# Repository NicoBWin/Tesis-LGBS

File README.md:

# Tesis-LGBS

Es el repositorio para la materia _Diseño de equipos electronico - 22.31_. Se basa en un Inverter de Corriente o también conocido como Convertidor Modular Multinivel de Corriente. El repo se divide en carpetas según los hitos que se fueron presentando, asi como tambíen se divide en diferentes carpeta segun reuniones, avance, o prototipado.

**Comienzo:** 06/03/2024

**Finalización:** ??/??/????

## Equipo

-   Linares, Gonzalo
-   Gullino, Agustín
-   Bustelo, Nicolás
-   Sergi, Damián

## Tutores

-   Aguirre, Pablo Miguel
-   Cossutta, Pablo Martín

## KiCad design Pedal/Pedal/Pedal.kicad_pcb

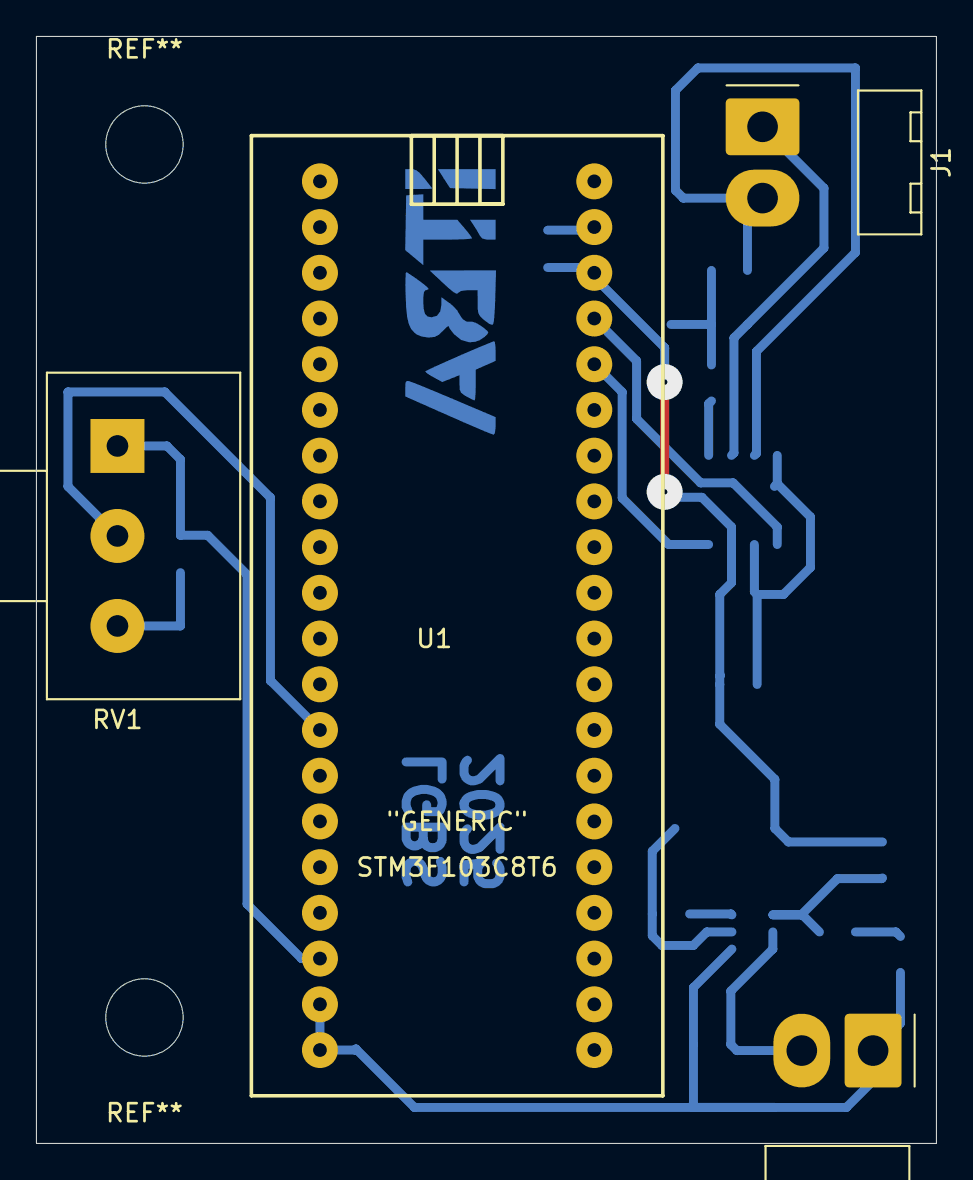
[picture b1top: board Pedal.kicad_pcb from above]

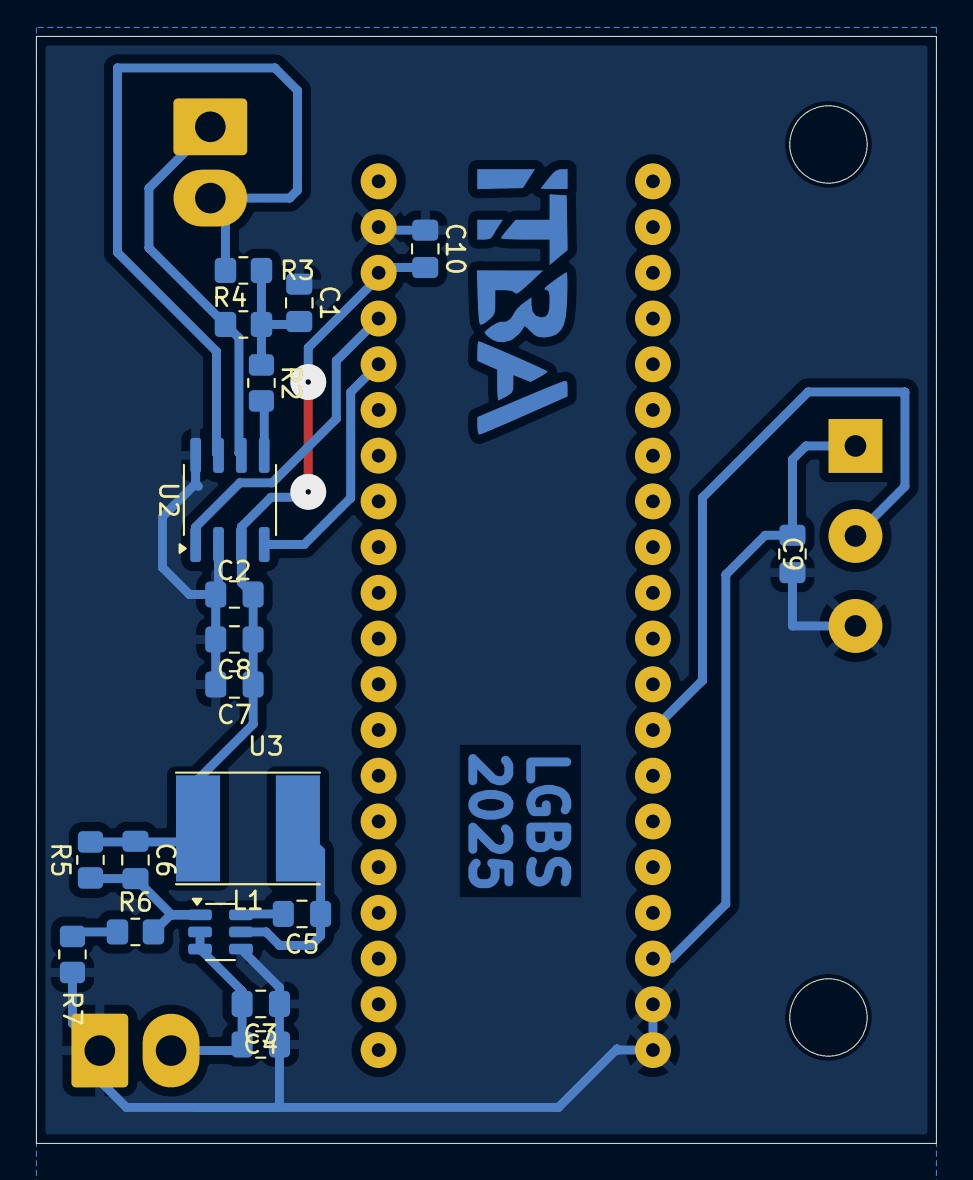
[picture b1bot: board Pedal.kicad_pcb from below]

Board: 2 copper layers, 50.0 x 61.5 mm, 23 parts (19 on the bottom side), 15 nets.

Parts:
C1: 4.7nF; C_0805_2012Metric_Pad1.18x1.45mm_HandSolder
C2, C3, C5, C9: 100nF; C_0805_2012Metric_Pad1.18x1.45mm_HandSolder
C4, C7, C8: 10uF; C_0805_2012Metric_Pad1.18x1.45mm_HandSolder
C6: 100pF; C_0805_2012Metric_Pad1.18x1.45mm_HandSolder
C10: 1uF; C_0805_2012Metric_Pad1.18x1.45mm_HandSolder
J1, J2: Conn_01x02; Molex_KK-396_A-41792-0002_1x02_P3.96mm_Horizontal
L1: 10uH; L_Taiyo-Yuden_NR-60xx_HandSoldering
R2: 300; R_0805_2012Metric_Pad1.20x1.40mm_HandSolder
R3, R4: 61; R_0805_2012Metric_Pad1.20x1.40mm_HandSolder
R5: 10k; R_0805_2012Metric_Pad1.20x1.40mm_HandSolder
R6: 1.8k; R_0805_2012Metric_Pad1.20x1.40mm_HandSolder
R7: 100; R_0805_2012Metric_Pad1.20x1.40mm_HandSolder
RV1: 100k; Potentiometer_Alps_RK163_Single_Horizontal
U1: YAAJ_BluePill_Part_Like; BLUEPILL
U2: MCP2561-E-SN; SOIC-8_3.9x4.9mm_P1.27mm
U3: AP63200WU; TSOT-23-6

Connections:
+3.3V: C9.1, RV1.1, U1.38 (3V3)
+5V: C2.1, C6.1, C7.1, C8.1, C10.2, L1.2, R5.2, U1.18 (5V), U2.3 (VDD)
+24V: C3.2, C4.2, J2.2, U3.2 (EN), U3.3 (IN)
CAN_RXD: U1.16 (PB8), U2.4 (RXD)
CAN_TXD: U1.17 (PB9), U2.1 (TXD)
GND: C1.1, C2.2, C3.1, C4.1, C7.2, C8.2, C9.2, C10.1, J2.1, R7.1, RV1.3, U1.19 (GND), U1.39 (GND), U1.40 (GND), U2.2 (VSS), U2.8 (STBY), U3.4 (GND)
unnamed: C1.2, R2.1, R3.1, R4.2
unnamed: J1.1, R4.1, U2.6 (CANL)
unnamed: J1.2, R3.2, U2.7 (CANH)
unnamed: R6.1, R7.2
unnamed: R2.2, U2.5 (SPLIT)
unnamed: C5.2, U3.6 (BST)
unnamed: C6.2, R5.1, R6.2, U3.1 (FB)
unnamed: C5.1, L1.1, U3.5 (SW)
POT_VALUE: RV1.2, U1.33 (PB0)

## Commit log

2024-03-29 add papers
2024-05-14 ReunionMiguel
2024-05-14 Arreglo al apunte de reunion de Miguel 13-05
2024-05-16 datasheet motor, preguntas a miguel, papers
2024-05-23 clase consultas 22-05
2024-05-23 Added Excel Trazabilidad
2024-05-24 add presentacion hito 1 and modify readme
2024-06-01 Acomodar
2024-06-08 Add Hito1
2024-08-13 actualización de comentarios.
2024-08-23 Reunión 23-08-24
2024-09-27 added some dummy files
2024-09-29 evironment created
2024-09-29 a ver si anda
2024-09-29 ahi lo arregle
2024-09-29 move .env
2024-09-29 moved some files
2024-09-29 probando
2024-09-29 ahora anda
2024-09-29 some updates
2024-09-29 UART ready to test
2024-09-29 estoy programando el top-v para hacer un lookback
2024-10-05 bueno, todavia no me anda
2024-10-05 reverted .pfc
2024-10-05 added tb
2024-10-05 creo que la transmision anda
2024-10-05 falta que ande la RX
2024-10-06 a ver si ahora anda
2024-10-06 probando...
2024-10-07 todavia no anda, esta raro
2024-10-07 ahora anda mejor
2024-10-10 generator created
2024-10-12 some changes
2024-10-12 now tx works better
2024-10-14 testing rx
2024-10-15 trying to program generators
2024-10-15 added generator
2024-10-16 no se que le pasa a la frecuencia
2024-10-16 listo
2024-10-18 pingocha
2024-10-18 agregamos papers
2024-10-20 updated tx
2024-10-20 phase gen erased
2024-10-20 uart tx refactored
2024-10-20 a ver
2024-10-20 reverted tx
2024-10-20 esta version puede que este mejor
2024-10-20 ready rx to test
2024-10-21 added docs
2024-10-21 trying to redo generator
2024-10-21 ready to test uart
2024-10-21 utils clk divider needs to be fixed
2024-10-21 added shift register
2024-10-27 se podria probar ya el ADC
2024-10-27 listo XD
2024-10-27 minor changes
2024-10-28 modifique tx
2024-10-31 test
2024-10-31 added tbs
2024-10-31 moved some code
2024-10-31 modifed makefiles
2024-10-31 fixed ADC
2024-10-31 hice lo que se pudio
2024-11-02 probemos esto
2024-11-02 agregamos archivos de matlab
2024-11-07 cambios que hizo gonza el sabado en el cidei
2024-11-08 read main to test
2024-11-08 folders for hitos
2024-11-08 to-do
2024-11-09 ToDo_Modificacion
2024-11-09 listo el adc
2024-11-09 Reorganizacion
2024-11-09 Arreglito
2024-11-09 Reorganizacion 2.0
2024-11-16 fixed
2024-11-16 erased const source
2024-11-16 ready uart
2024-11-23 some changes in makefile
2024-11-25 mejorando UART
2024-11-26 no changes
2024-11-26 mejore la velocidad pero no anda mejor el transmisor
2024-11-26 added manchester
2024-11-27 erased
2024-11-27 no andaaa nadaa
2024-11-27 el uart de springler
2024-11-27 reverted UART
2024-11-27 nada
2024-12-01 matlab changes
2024-12-01 changes in tx and rx
2024-12-01 added hamming code
2024-12-02 modificando RX
2024-12-04 anda muuucho mejor
2024-12-04 anda raro algo del receptor
2024-12-20 Matlab Modulation is ready to test
2024-12-24 seguimo' sumando codigo del SPI
2024-12-29 testing
2025-01-03 tested
2025-01-03 haciendo el top main FPGA
2025-01-03 ready to verify
2025-01-03 verified
2025-01-04 Blackpill folder erased
2025-01-06 writing pipe
2025-01-08 updated matlab hdl model
2025-01-08 matlab update
2025-01-09 writing modules
2025-01-11 programming modules
2025-01-11 added tasks to modules
2025-01-11 spi_tb updated
2025-01-16 changes in schematic
2025-01-17 modifying main FPGA
2025-01-17 added more lines
2025-01-17 no creo que ande esto
2025-01-18 La modulacion tiene un revamp
2025-01-18 modifications in uart_tx
2025-01-18 te subo el RX
2025-01-18 codigo
2025-01-18 mira
2025-01-18 anda RX
2025-01-19 subo
2025-01-19 cuack
2025-01-19 parece andar
2025-01-21 Actualiza el Makefile y módulos UART para mejorar la transmisión y recepción de datos
2025-01-21 Corrige la señal de reloj en el módulo uart_tx y actualiza la asignación de pines en top_UART_TX
2025-01-21 Modifica el estado inicial en el módulo uart_tx y actualiza la asignación de pines en top_UART_TX
2025-01-21 tengo que revisar la task ....
2025-01-22 Actualiza la tasa de baudios a 6M en el módulo top_UART_TX y simplifica la lógica de finalización de transmisión
2025-01-22 Actualiza el Makefile y módulos UART para cambiar la tasa de baudios a 1M y renombrar el módulo de prueba
2025-01-22 Crea el módulo top_UART_loopback y actualiza el Makefile para incluirlo, además de modificar la asignación de pines en el módulo de prueba.
2025-01-22 Modifica el módulo uart_rx para ampliar el tamaño del estado y añade el estado RX_DONE. Actualiza la lógica en top_UART_loopback para manejar la transmisión y recepción de datos correctamente.
2025-01-25 ultima
2025-01-25 Actualiza el Makefile y los módulos de prueba UART para corregir la asignación de pines y ajustar la lógica de temporización.
2025-01-25 Actualiza el Makefile y modifica el módulo top_prueba_UART_UB para corregir la lógica de transmisión y recepción de datos.
2025-01-25 Actualiza el Makefile y modifica los módulos de prueba UART para corregir la asignación de nombres y mejorar la lógica de transmisión.
2025-01-25 Actualiza la configuración del oscilador y la tasa de baudios en los módulos de prueba UART.
2025-01-25 Actualiza el Makefile y los módulos de prueba UART para corregir la asignación de nombres y ajustar la configuración del oscilador y la tasa de baudios.
2025-01-25 Modifica la lógica de recepción y transmisión en los módulos UART para mejorar el manejo de estados y la sincronización de señales.
2025-01-25 Reorganiza la asignación de señales en el módulo de prueba UART para mejorar la claridad y el manejo de datos recibidos.
2025-01-27 1Mb/s varios cambios
2025-02-01 UART_Avances6Mb/s
2025-02-01 Mejor documentado UART
    UART funciona a 6Mb/s de forma constante pero con STOP = 2
2025-02-01 review SPI
2025-02-01 Renombra el estado DESELECT a DONE en el módulo SPI para mejorar la claridad del flujo de estado.
2025-02-01 Add top module for SPI and update clock rates; remove unused UART_RX module
2025-02-02 Add PRAM module and update top module to replace RAM; refactor SPI connections
2025-02-03 Add schematics
2025-02-07 no anda spi
2025-02-08 test ready
2025-02-08 updated SPI
2025-02-09 cambios en sclk
2025-02-09 reverted
2025-02-19 agregue codigo en la fpga main
2025-02-22 micro
2025-02-22 Simulations with real current source and ajusted correctly the pins used
2025-02-22 SPI_Funciona el codigo nuevo masomenos
2025-02-22 CAN SPI
2025-02-23 added a pram testbench
2025-02-23 ready PRAM
2025-03-01 Test Main current source
2025-03-01 Add MAX_CURR constant and input validation in set_I function
2025-03-01 done current
2025-03-03 Some sims update
2025-03-05 ytfytd
2025-03-07 casi casi
2025-03-07 bueno, listo por hoy
2025-03-08 add binary files and history for Tesis_LGBS project
2025-03-08 escribiendo el main PFAGA
2025-03-08 added maximum calc
2025-03-08 Add mediciones
    Just Buck & Flyback
2025-03-08 module
2025-03-08 toma
2025-03-09 colors modified
2025-03-09 jdsjfaosjdaj
2025-03-09 asdasd
2025-03-09 sadasdasdasd
2025-03-09 toma papa
2025-03-09 jajaja
2025-03-10 subi el tb
2025-03-10 ni idea che
2025-03-15 Refactor FPGA modules and update MATLAB simulation files
2025-03-15 Update MATLAB simulation and enhance FPGA system output with sine wave LUT
2025-03-15 agregue diagrama
2025-03-15 agregando comentarios
2025-03-15 agregamos mas comentarios
2025-03-15 creo que estan listos los sources
2025-03-15 listo top main FPGA
2025-03-16 done
2025-03-17 deglitched but no dead time
2025-03-18 Dios nos salve
2025-03-20 40 repeat points
2025-03-22 confiabilidad
2025-03-22 subilo Agus
2025-03-22 oijoij
2025-03-22 cambiando el tb de la modulacion
2025-03-22 reveted buffer
2025-03-22 listo la triangular
2025-03-22 probalo maquina
2025-03-22 ahora si
2025-03-22 yuggyug
2025-03-23 Salvenme
2025-03-23 shoot mas largo
2025-03-29 listo confiabilidad
2025-04-02 lista la confiabilidad
2025-04-02 camibos
2025-04-06 Tal vez funcione
2025-04-06 5 modules
2025-04-06 avanzando
2025-04-06 added pedal schematics and pcb
2025-04-06 added sch
2025-04-10 lista la placa para imprimir
2025-04-11 listorti
2025-04-11 stm arreglada
2025-04-12 testeando
2025-04-12 asda
2025-04-13 fixes
2025-04-13 initial commit del programa del pedal
2025-04-13 subi el codigo
2025-04-18 listillo el pedal
2025-04-18 Matlab Dump
2025-04-18 ultimo
2025-04-18 bueno
2025-04-18 kjajajajaja
2025-04-19 anda
